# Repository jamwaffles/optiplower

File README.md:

# Optiplower

Dell Optiplex Power supply experiments.

I want to run a Dell Optiplex 3050 Micro off an industrial 24Vdc supply. Two issues:

1. The Dell takes 19.5v
2. It will refuse to clock above 800MHz if it can't communicate with the charger to check how much
   power it can provide.

This project aims to solve both by incorporating:

1. A 5A DCDC converter to give 19.5v from 24v input
2. Either an ATTiny85 or a DS2502 to communicate with the mainboard and spoof it into thinking it
   has a 65W PSU attached.

Onto a single, tiny PCB that can be hidden away inside the Dell.

References:

- <https://github.com/KivApple/dell-charger-emulator>
- <https://github.com/garyStofer/DS2502_DELL_PS>
- <https://github.com/timothyjager/DellPSU>
- <https://www.instructables.com/Embedded-EEPROM-Into-DELL-Laptop-for-Charger-Ident/>
- <https://github.com/HclX/DELL_POWER_SPOOFER>
- <https://blog.project-insanity.org/2020/05/25/hardware-fix-for-dell-ac-power-adapter-could-not-be-determined/>
- Among others

Please use KiCAD 7 to open the board files. The PSU uses JLC/LCSC-sourcable parts if you'd like to
build your own.

DigiSpark ATTiny85 devboard LED is connected to PB0

## Connection

The output connector is designed for a 5-way 1.27mm pitch ribbon cable. The 5 pins mirror the layout
of the pins on the barrel jack PCB connector.

## Sample dumps

- `DELL00AC090195046CN09T` (90w) from
  <https://github.com/garyStofer/DS2502_DELL_PS/blob/master/DS2502_DELL_PS.ino> or
  `DELL00AC090195046CN09T2157161543835EAL03` with checksum
- `"DELL00AC045195023CN0CDF577243865Q27F2A05=\x94"` (45w)

## Firmware setup

Uses Arduino CLI

```bash
curl -fsSL https://raw.githubusercontent.com/arduino/arduino-cli/master/install.sh | BINDIR=~/.local/bin sh
```

## Programming

You'll need to edit the `memory` variable in `ds2502-emulator/src/DS2502.h` to change how the
charger identifies.

```bash
cd ds2502-emulator

make

make program

make fuses
```

Works with ATTiny25-10SSU, but can be made to target ATTiny85, etc by modifying the `AVRDUDE_MCU?`
line in `./ds2502-emulator/Makefile` along with the `fqbn...` line in
`./ds2502-emulator/sketch.yaml`.

## Burning bootloader issues

> Don't actually need to use the bootloader - I can use the USBASP directly. This section is just
> left here as a note.

Arduino IDE 2.x, "burn bootloader" with usbasp programmer selected.

Need to swap out programmer for the one on the system or various lib versions won't match, e.g.

```
error while loading shared libraries: libtinfo.so.5: cannot open shared object file: No such file or directory
```

E.g.

```bash
mv /home/james/.arduino15/packages/arduino/tools/avrdude/6.0.1-arduino5/bin/avrdude /home/james/.arduino15/packages/arduino/tools/avrdude/6.0.1-arduino5/bin/avrdude_old
ln -s $(which avrdude) /home/james/.arduino15/packages/arduino/tools/avrdude/6.0.1-arduino5/bin/avrdude
```

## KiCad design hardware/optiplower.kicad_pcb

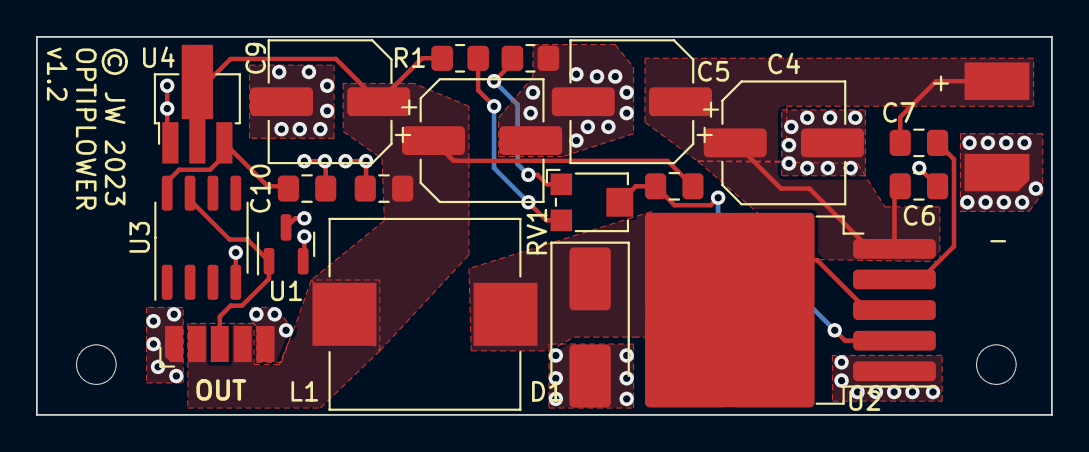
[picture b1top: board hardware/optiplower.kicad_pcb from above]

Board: 2 copper layers, 56.4 x 21.0 mm, 22 parts (0 on the bottom side), 10 nets.

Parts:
C4, C5, C9, C11: 220uF; CP_Elec_6.3x7.7
C6, C7, C10, C12: 1uF; C_0805_2012Metric_Pad1.18x1.45mm_HandSolder
C8: 33n; C_0805_2012Metric_Pad1.18x1.45mm_HandSolder
D1: SK84B; D_SMB_Handsoldering
H1, H2: MountingHole_2.2mm_M2
J1: Conn_01x02; 5.08_PWR_IN
J2: Conn_01x03; Output_pads
L1: 47uH; L_MDA1050_10x11mm
R1: 150K; R_0805_2012Metric_Pad1.20x1.40mm_HandSolder
R2: 10K; R_0805_2012Metric_Pad1.20x1.40mm_HandSolder
RV1: 1K; Potentiometer_Bourns_TC33X_Vertical
U1: DS2502S+; SOT-23
U2: XL4015; TO-263-5_TabPin3
U3: ATtiny25-10SSU; SOIC-8_3.9x4.9mm_P1.27mm
U4: LR7533-M; SOT-89-3_Handsoldering

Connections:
+3V3: C10.1, U3.8 (VCC), U4.3 (VO)
+24V: C4.1, C5.1, C6.1, C7.1, J1.1, U2.5 (VIN)
/SENSE: J2.3, U1.1 (SDQ), U3.7 (PB2)
/SW: D1.1 (K), L1.1, U2.3 (SW)
GND: C4.2, C5.2, C6.2, C9.2, C10.2, C11.2, C12.2, D1.2 (A), J1.2, J2.1, J2.5, R2.2, U1.2 (VSS), U1.3 (VSS), U2.1 (GND), U3.4 (GND), U4.1 (GND)
unnamed: R1.2, RV1.3
unnamed: R2.1, RV1.1
unnamed: C8.2, RV1.2, U2.2 (FB)
unnamed: C7.2, U2.4 (VC)
VCC: C8.1, C9.1, C11.1, C12.1, J2.2, J2.4, L1.2, R1.1, U4.2 (VI)

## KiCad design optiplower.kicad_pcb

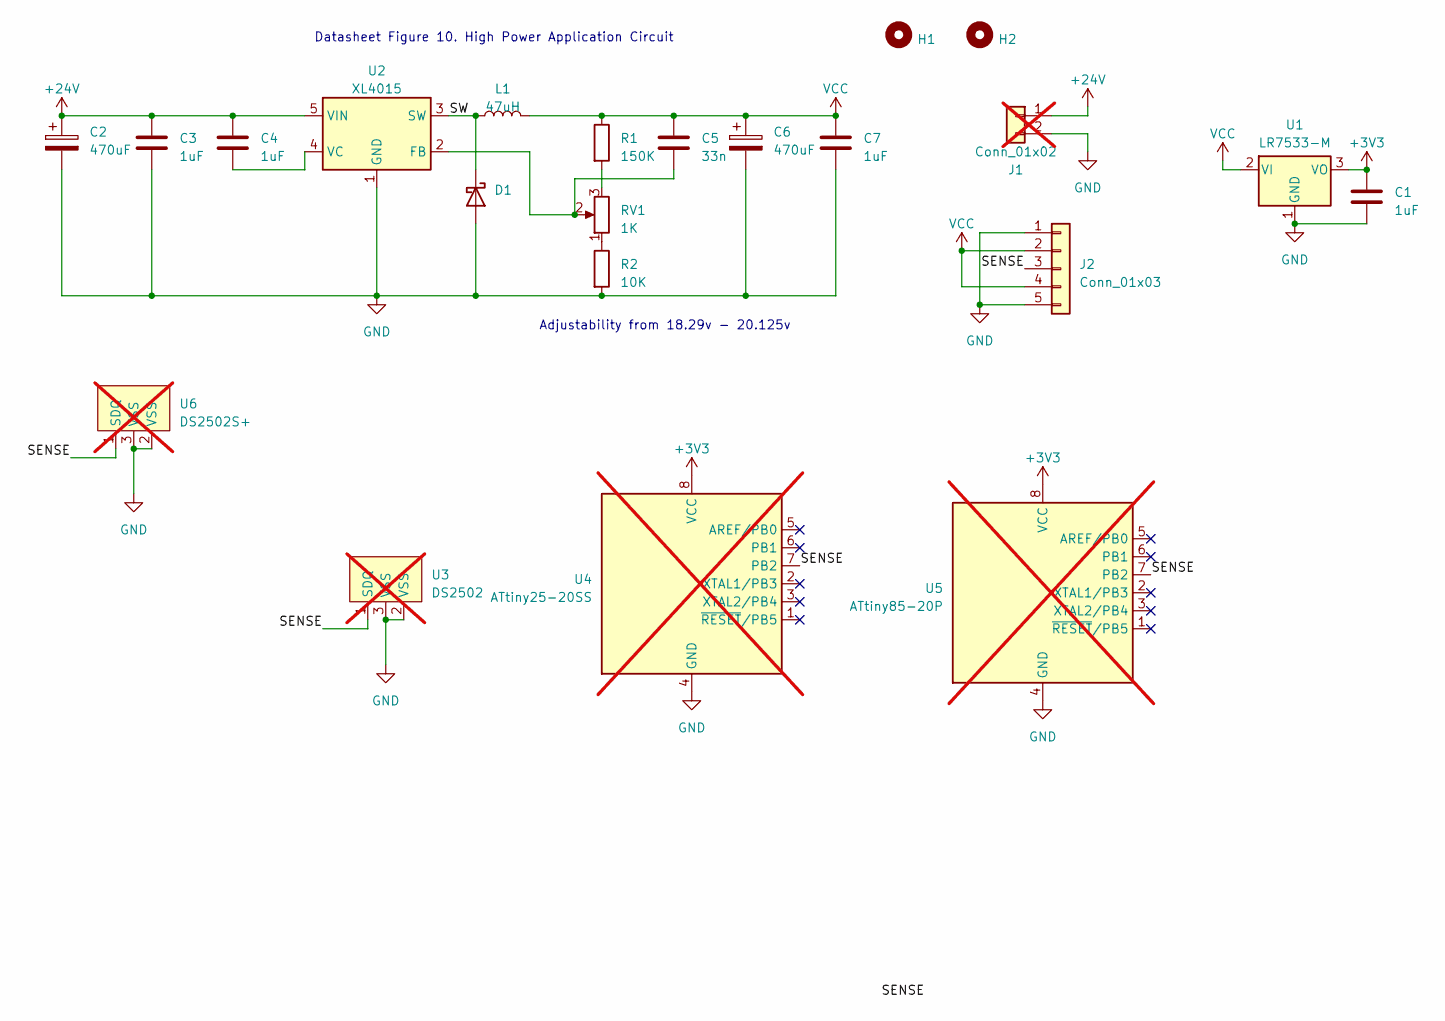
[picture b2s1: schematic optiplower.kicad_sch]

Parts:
C1, C3, C4, C7: 1uF; C_0805_2012Metric_Pad1.18x1.45mm_HandSolder; LCSC C28323
C2, C6: 470uF; CP_Radial_D8.0mm_P3.50mm_H11.5; MPN 25PX470MEFC8X11.5; LCSC C88730
C5: 33n; C_0805_2012Metric_Pad1.18x1.45mm_HandSolder; LCSC C1739
D1: SK84B; D_SMB_Handsoldering; MPN SK84B; LCSC C65016
H1, H2: MountingHole_2.2mm_M2
J1: Conn_01x02; 5.08_PWR_IN; not fitted
J2: Conn_01x03; PinHeader_1x05_P1.27mm_Vertical
L1: 47uH; L_MDA1050_10x11mm; MPN MDA1050-470M; LCSC C2847567
R1: 150K; R_0805_2012Metric_Pad1.20x1.40mm_HandSolder; LCSC C17470
R2: 10K; R_0805_2012Metric_Pad1.20x1.40mm_HandSolder; LCSC C17414
RV1: 1K; Potentiometer_Bourns_TC33X_Vertical; MPN TC33X-2-102E; LCSC C719174
U1: LR7533-M; SOT-89-3_Handsoldering; MPN LR7533-M; LCSC C486076
U2: XL4015; TO-263-5_TabPin3; MPN XL4015E1; LCSC C51661
U3: DS2502; TO-92_Inline; not fitted
U4: ATtiny25-20SS; SOIC-8_3.9x4.9mm_P1.27mm; LCSC C615549; not fitted
U5: ATtiny85-20P; DIP-8_W7.62mm; LCSC C965497; not fitted
U6: DS2502S+; SOT-23; not fitted

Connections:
+3V3: C1.1, U1.3 (VO), U4.8 (VCC), U5.8 (VCC)
+24V: C2.1, C3.1, C4.1, J1.1, U2.5 (VIN)
/SENSE: J2.3, U3.1 (SDQ), U4.7 (PB2), U5.7 (PB2), U6.1 (SDQ)
/SW: D1.1 (K), L1.1, U2.3 (SW)
GND: C1.2, C2.2, C3.2, C6.2, C7.2, D1.2 (A), J1.2, J2.1, J2.5, R2.2, U1.1 (GND), U2.1 (GND), U3.2 (VSS), U3.3 (VSS), U4.4 (GND), U5.4 (GND), U6.2 (VSS), U6.3 (VSS)
unnamed: R1.2, RV1.3
unnamed: R2.1, RV1.1
unnamed: C5.2, RV1.2, U2.2 (FB)
unnamed: C4.2, U2.4 (VC)
VCC: C5.1, C6.1, C7.1, J2.2, J2.4, L1.2, R1.1, U1.2 (VI)

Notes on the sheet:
Adjustability from 18.29v - 20.125v
Datasheet Figure 10. High Power Application Circuit

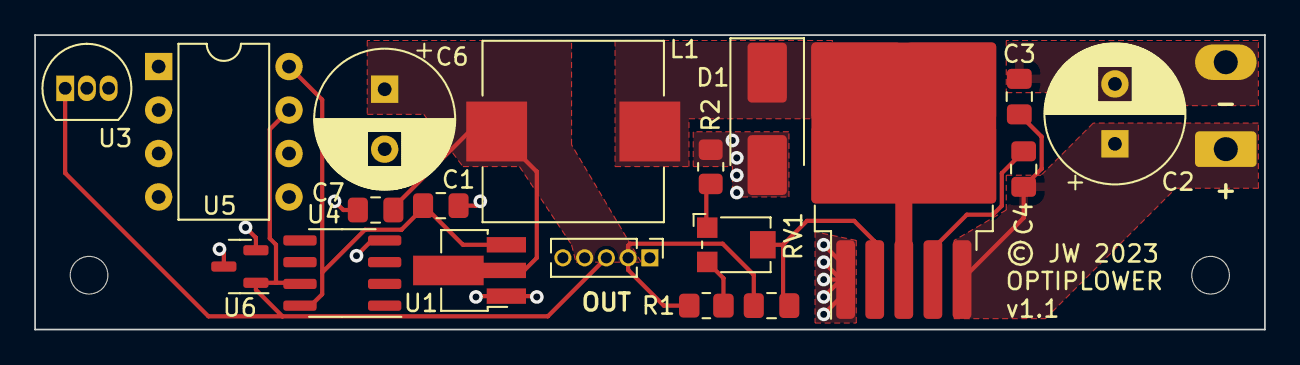
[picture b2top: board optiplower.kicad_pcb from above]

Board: 2 copper layers, 71.9 x 17.2 mm, 22 parts (0 on the bottom side), 10 nets.

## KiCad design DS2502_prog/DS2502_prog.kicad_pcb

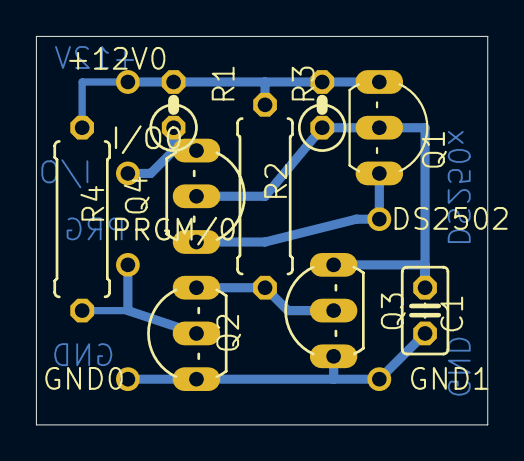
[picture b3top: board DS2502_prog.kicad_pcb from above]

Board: 2 copper layers, 25.1 x 21.6 mm, 15 parts (0 on the bottom side), 7 nets.

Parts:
+12V0: SOLDER_POINTA; P1-13
C1: 470pf; C025-025X050
DS2502: SOLDER_POINTA; P1-13
GND0, GND1: SOLDER_POINTA; P1-13
I/O0: SOLDER_POINTA; P1-13
PRGM/0: SOLDER_POINTA; P1-13
Q1: VP0106N3; TO92-
Q2, Q3, Q4: 2N7000; TO92-LINE
R1: 4.7K; 0207_2V
R2: 10k; 0309_10
R3: 10K; 0207_2V
R4: 100k; 0309_10

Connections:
unnamed: +12V0.1, Q1.3, R1.2, R2.2, R3.2, R4.2
unnamed: I/O0.1, Q4.3, R1.1
unnamed: Q2.1, Q3.2, R2.1
unnamed: PRGM/0.1, Q2.2, R4.1
unnamed: C1.2, GND0.1, GND1.1, Q2.3, Q3.3
unnamed: C1.1, Q1.2, Q3.1, Q4.2, R3.1
unnamed: DS2502.1, Q1.1, Q4.1

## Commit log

2023-03-24 Schematic, most footprints
2023-03-24 V3 with upside down regulator
2023-03-24 Add LMR14050 part
2023-03-24 Stuff
2023-03-24 Use JLC basic parts for some things
2023-03-24 Production files
2023-03-24 Readme and images
2023-03-27 Fix ATTiny part numbers for footprint
2023-03-27 Firmware and dumps to spoof charger
2023-03-27 Notes and images and stuff
2023-03-27 More links
2023-03-28 Disable pullups to increase drive voltage
2023-03-28 Add some scope captures
2023-03-28 Add DS2502 blank ROM maps
2023-03-28 Add hex dump from cannibalised Dell 65w charger
2023-03-28 PCB shots of Dell 65W charger
2023-03-28 Link
2023-03-28 Add half done programmer board
2023-03-29 WIP programmer design restart
2023-03-29 Correct ATTiny PN
2023-03-29 LCSC parts
2023-03-29 Calibrate crappy ATTiny clock
2023-03-29 Format
2023-03-29 More oscillator calibration
2023-03-29 Messing around trying to get timings right in PulseView
2023-03-29 Fix high level at startup
2023-03-30 Arduino notes
2023-03-30 65W charger trace
2023-03-30 Arduino FW using OneWireHub
2023-03-30 Move PCB into hardware/ folder
2023-03-30 Works with Arduino!
2023-03-30 Use local copy of OneWireHub
2023-03-30 Remove unused devices
2023-03-30 Reduce code size a bit
2023-03-30 Arduino CLI build
2023-03-30 Clean up OneWireHub
2023-03-30 Remove Serial.println, run format
2023-03-30 Trying to make it work on ATTiny25
2023-03-30 Gut a bunch of OneWireHub
2023-03-30 Give up on ATTiny25 for now
2023-03-30 Fresh OneWireHub fork
2023-03-30 Shrink a bit
2023-03-30 Rip out some stuff
2023-03-30 Remove getIndexOfNextSensorInList
2023-03-30 Remove some command handling we don't need
2023-03-30 Remove even more commands
2023-03-30 Remove nearly all command handling
2023-03-30 Remove USE_GPIO_DEBUG
2023-03-30 Remove slave_selected, make slave_list a single item
2023-03-30 Remove slave_count, id_tree, etc
2023-03-30 Remove configurability
2023-03-30 Remove some error handling
2023-03-30 Reduce mem page size
2023-03-30 Fixed mem size
2023-03-30 Get rid of memcpy
2023-04-09 Fix 3.3v regulator pinout
2023-04-09 Update part details
2023-04-09 Make design completely SMD
2023-04-12 Use ATTiny25
2023-04-17 Update gerbers for latest SMD spin
2023-04-17 Add ATTiny to BOM
2023-04-17 Update images
2023-04-17 Fix readme
2023-06-20 PCB thickness to 0.8mm
2023-07-03 Convert everything to STEP so export works
2023-07-08 Relayout so caps fit in gap
2023-07-08 v1.1 sent to fab
2023-07-22 Update readme images
2023-07-22 Improve instructions on changing target MCU
2023-07-22 Add "Vanity" 3D view for readme captures
2023-12-12 Add connection diagram
2023-12-13 Rust firmware skeleton with RTIC
2023-12-13 Quick lil discover binary
    Works too!
2023-12-14 Discover/FW split
2023-12-14 Edge detect task
2023-12-14 Remove old junk
2023-12-14 Remove a bunch of commented out code
2023-12-24 Properly order output pins
    Closes #4

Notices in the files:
hardware/optiplower.kicad_pcb:
© JW 2023
